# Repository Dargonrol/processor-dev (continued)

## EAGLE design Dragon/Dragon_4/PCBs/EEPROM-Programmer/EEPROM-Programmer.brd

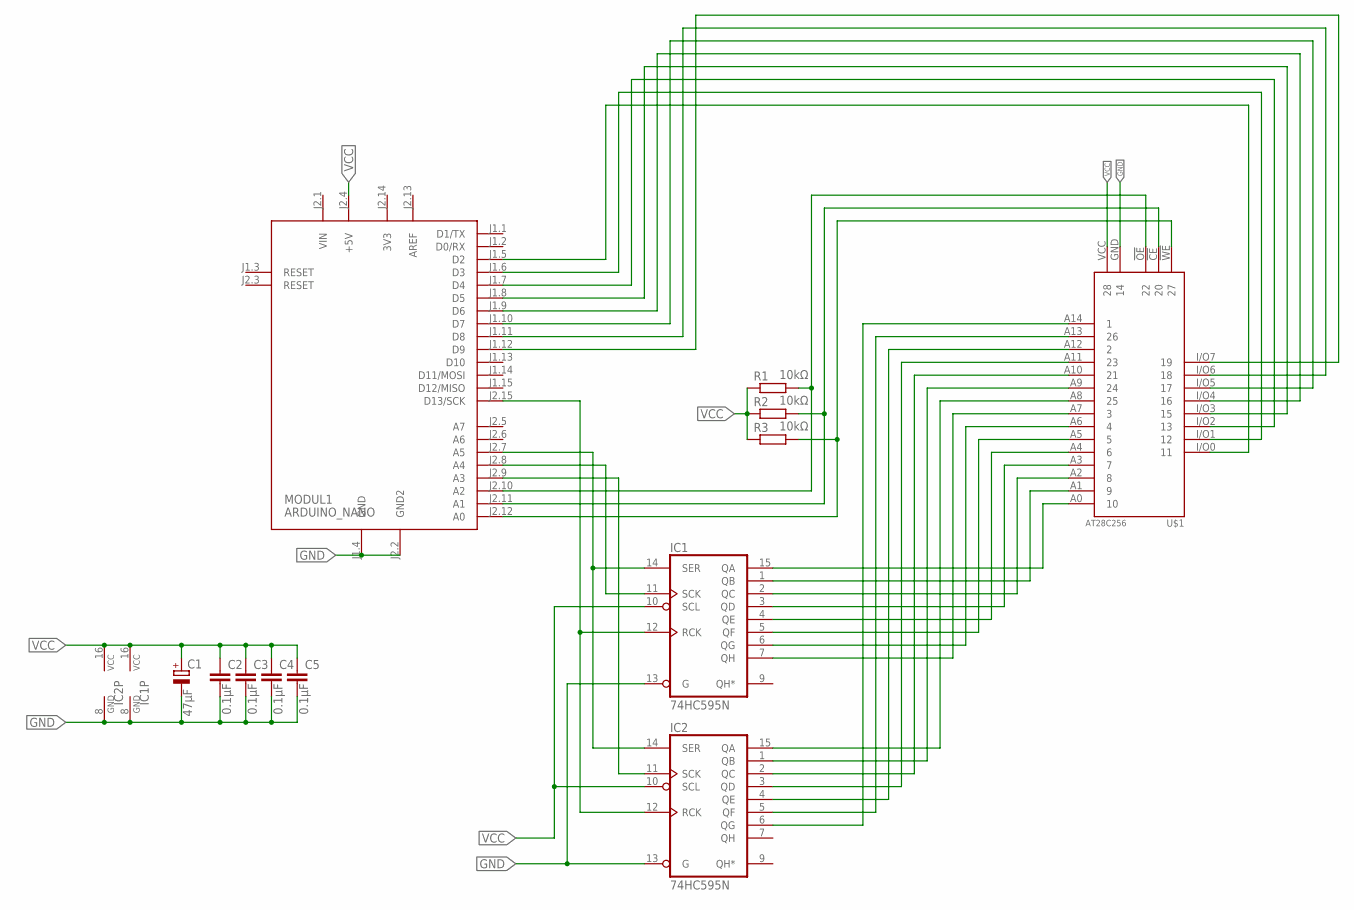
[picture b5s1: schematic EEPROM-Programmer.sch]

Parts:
C1: 47µF; E2,5-6E
C2, C3, C4, C5: 0.1µF; C2.5-3
IC1, IC2: 74HC595N; DIL16
MODUL1: ARDUINO_NANO; ARDUINO_NANO2
R1, R2, R3: 10kΩ; 0204/7
U$1: AT28C256

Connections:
3V3: MODUL1.J2.14 (3V3)
AREF: MODUL1.J2.13 (AREF)
GND: C1.-, C2.2, C3.2, C4.2, C5.2, IC1.8 (GND), IC1.13 (G), IC2.8 (GND), IC2.13 (G), MODUL1.J1.4 (GND), MODUL1.J2.2 (GND2), U$1.GND (14)
unnamed: IC1.15 (QA), U$1.A0 (10)
unnamed: IC1.1 (QB), U$1.A1 (9)
unnamed: IC1.2 (QC), U$1.A2 (8)
unnamed: IC1.3 (QD), U$1.A3 (7)
unnamed: IC1.4 (QE), U$1.A4 (6)
unnamed: IC1.5 (QF), U$1.A5 (5)
unnamed: IC1.6 (QG), U$1.A6 (4)
unnamed: IC1.7 (QH), U$1.A7 (3)
unnamed: IC2.15 (QA), U$1.A8 (25)
unnamed: IC2.1 (QB), U$1.A9 (24)
unnamed: IC2.2 (QC), U$1.A10 (21)
unnamed: IC2.3 (QD), U$1.A11 (23)
unnamed: IC2.4 (QE), U$1.A12 (2)
unnamed: IC2.5 (QF), U$1.A13 (26)
unnamed: IC2.6 (QG), U$1.A14 (1)
unnamed: MODUL1.J1.5 (D2), U$1.I/O0 (11)
unnamed: MODUL1.J2.12 (A0), R3.2, U$1.!WE (27)
unnamed: MODUL1.J1.6 (D3), U$1.I/O1 (12)
unnamed: MODUL1.J1.7 (D4), U$1.I/O2 (13)
unnamed: MODUL1.J1.8 (D5), U$1.I/O3 (15)
unnamed: MODUL1.J1.9 (D6), U$1.I/O4 (16)
unnamed: MODUL1.J1.10 (D7), U$1.I/O5 (17)
unnamed: MODUL1.J1.11 (D8), U$1.I/O6 (18)
unnamed: MODUL1.J1.12 (D9), U$1.I/O7 (19)
unnamed: MODUL1.J2.11 (A1), R2.2, U$1.!CE (20)
unnamed: MODUL1.J2.10 (A2), R1.2, U$1.!OE (22)
unnamed: IC2.11 (SCK), MODUL1.J2.9 (A3)
unnamed: IC1.11 (SCK), MODUL1.J2.8 (A4)
unnamed: IC1.14 (SER), IC2.14 (SER), MODUL1.J2.7 (A5)
unnamed: IC1.12 (RCK), IC2.12 (RCK), MODUL1.J2.15 (D13/SCK)
VCC: C1.+, C2.1, C3.1, C4.1, C5.1, IC1.10 (SCL), IC1.16 (VCC), IC2.10 (SCL), IC2.16 (VCC), MODUL1.J2.4 (+5V), R1.1, R2.1, R3.1, U$1.VCC (28)
VIN: MODUL1.J2.1 (VIN)

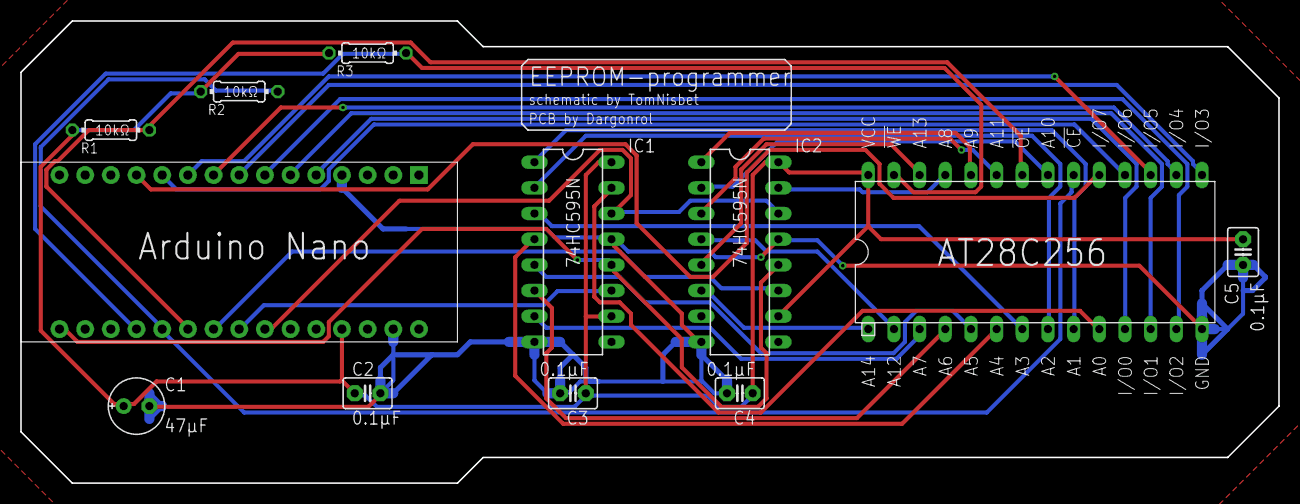
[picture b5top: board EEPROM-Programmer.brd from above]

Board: 2 copper layers, 124.5 x 45.7 mm, 12 parts (0 on the bottom side), 32 nets.

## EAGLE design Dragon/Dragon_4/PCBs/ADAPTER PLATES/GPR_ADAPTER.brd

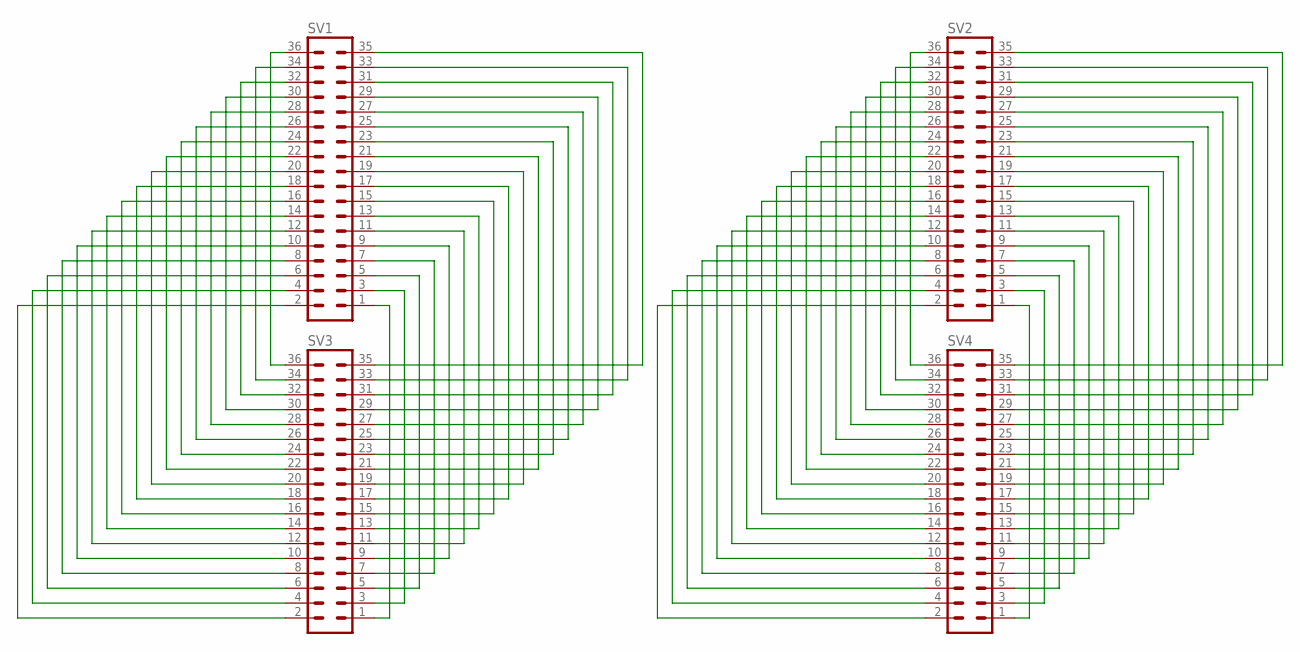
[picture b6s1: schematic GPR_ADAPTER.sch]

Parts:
SV1, SV2, SV3, SV4: MA18-2

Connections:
unnamed: SV1.36, SV3.36
unnamed: SV1.34, SV3.34
unnamed: SV1.32, SV3.32
unnamed: SV1.30, SV3.30
unnamed: SV1.28, SV3.28
unnamed: SV1.26, SV3.26
unnamed: SV1.24, SV3.24
unnamed: SV1.22, SV3.22
unnamed: SV1.20, SV3.20
unnamed: SV1.18, SV3.18
unnamed: SV1.16, SV3.16
unnamed: SV1.14, SV3.14
unnamed: SV1.12, SV3.12
unnamed: SV1.10, SV3.10
unnamed: SV1.8, SV3.8
unnamed: SV1.6, SV3.6
unnamed: SV1.4, SV3.4
unnamed: SV1.2, SV3.2
unnamed: SV2.34, SV4.34
unnamed: SV2.32, SV4.32
unnamed: SV2.30, SV4.30
unnamed: SV2.28, SV4.28
unnamed: SV2.26, SV4.26
unnamed: SV2.24, SV4.24
unnamed: SV2.22, SV4.22
unnamed: SV2.20, SV4.20
unnamed: SV2.18, SV4.18
unnamed: SV2.16, SV4.16
unnamed: SV2.14, SV4.14
unnamed: SV2.12, SV4.12
unnamed: SV2.10, SV4.10
unnamed: SV2.8, SV4.8
unnamed: SV2.6, SV4.6
unnamed: SV2.4, SV4.4
unnamed: SV2.2, SV4.2
unnamed: SV2.36, SV4.36
unnamed: SV1.3, SV3.3
unnamed: SV1.5, SV3.5
unnamed: SV1.7, SV3.7
unnamed: SV1.9, SV3.9
unnamed: SV1.11, SV3.11
unnamed: SV1.13, SV3.13
unnamed: SV1.15, SV3.15
unnamed: SV1.17, SV3.17
unnamed: SV1.19, SV3.19
unnamed: SV1.21, SV3.21
unnamed: SV1.23, SV3.23
unnamed: SV1.25, SV3.25
unnamed: SV1.27, SV3.27
unnamed: SV1.29, SV3.29
unnamed: SV1.31, SV3.31
unnamed: SV1.33, SV3.33
unnamed: SV1.35, SV3.35
unnamed: SV1.1, SV3.1
unnamed: SV2.3, SV4.3
unnamed: SV2.5, SV4.5
unnamed: SV2.7, SV4.7
unnamed: SV2.9, SV4.9
unnamed: SV2.11, SV4.11
unnamed: SV2.13, SV4.13
unnamed: SV2.15, SV4.15
unnamed: SV2.17, SV4.17
unnamed: SV2.19, SV4.19
unnamed: SV2.21, SV4.21
unnamed: SV2.23, SV4.23
unnamed: SV2.25, SV4.25
unnamed: SV2.27, SV4.27
unnamed: SV2.29, SV4.29
unnamed: SV2.31, SV4.31
unnamed: SV2.33, SV4.33
unnamed: SV2.35, SV4.35
unnamed: SV2.1, SV4.1

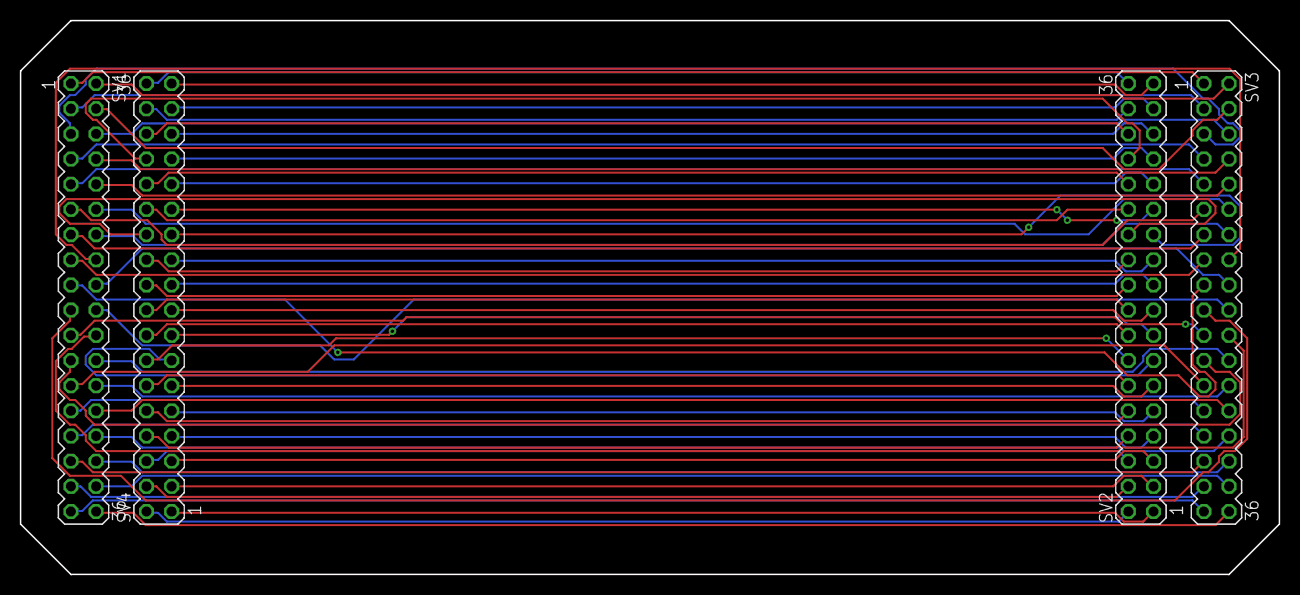
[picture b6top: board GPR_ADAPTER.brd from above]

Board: 2 copper layers, 127.0 x 55.9 mm, 4 parts (0 on the bottom side), 72 nets.

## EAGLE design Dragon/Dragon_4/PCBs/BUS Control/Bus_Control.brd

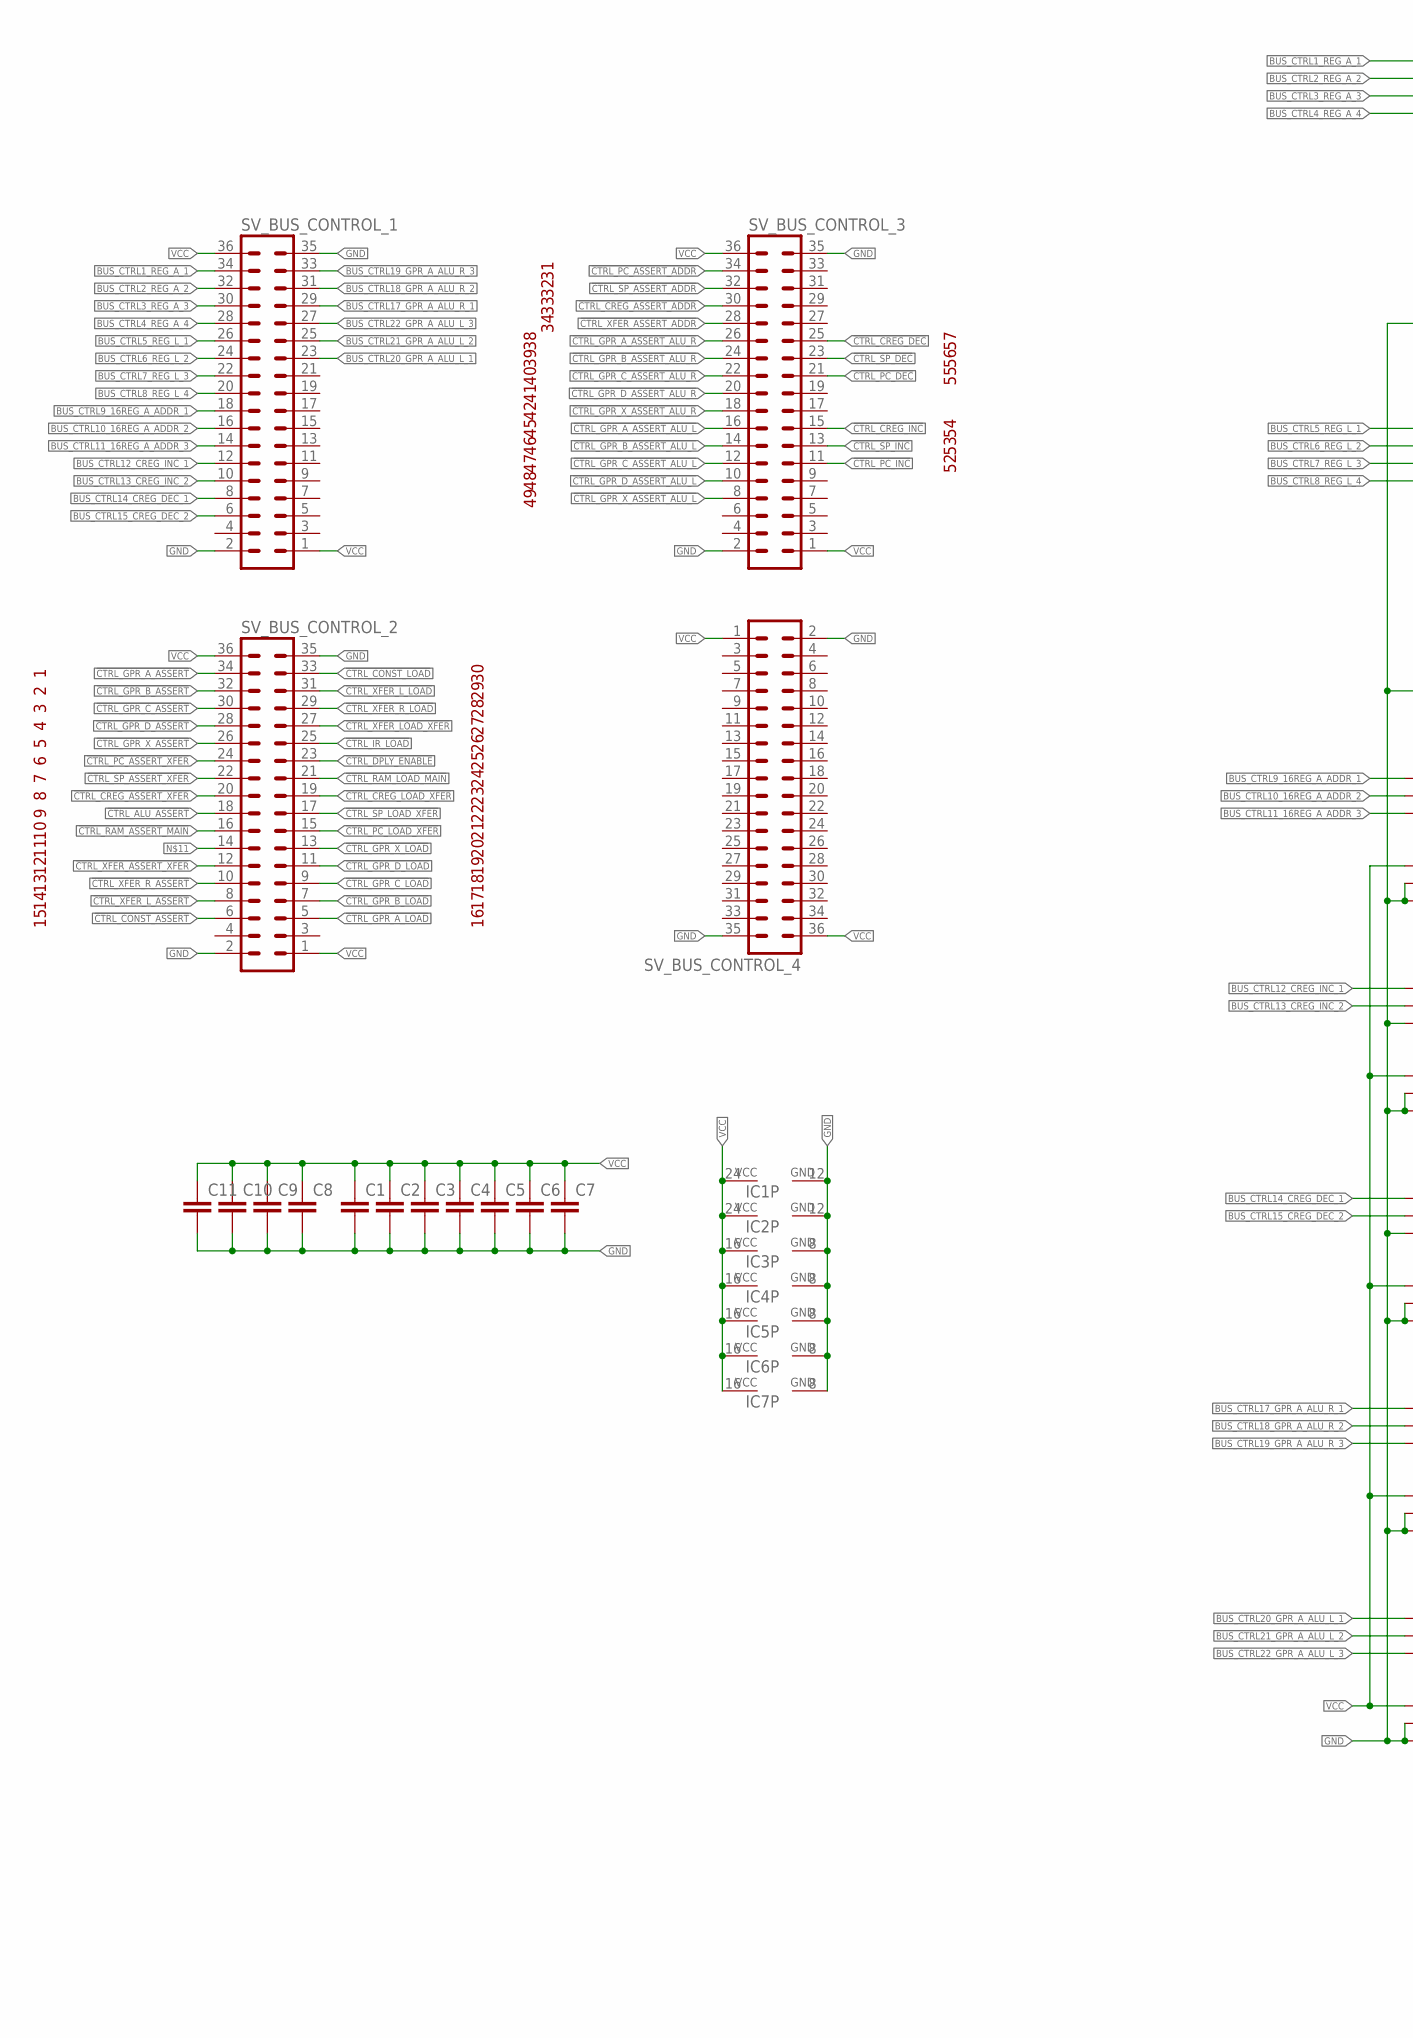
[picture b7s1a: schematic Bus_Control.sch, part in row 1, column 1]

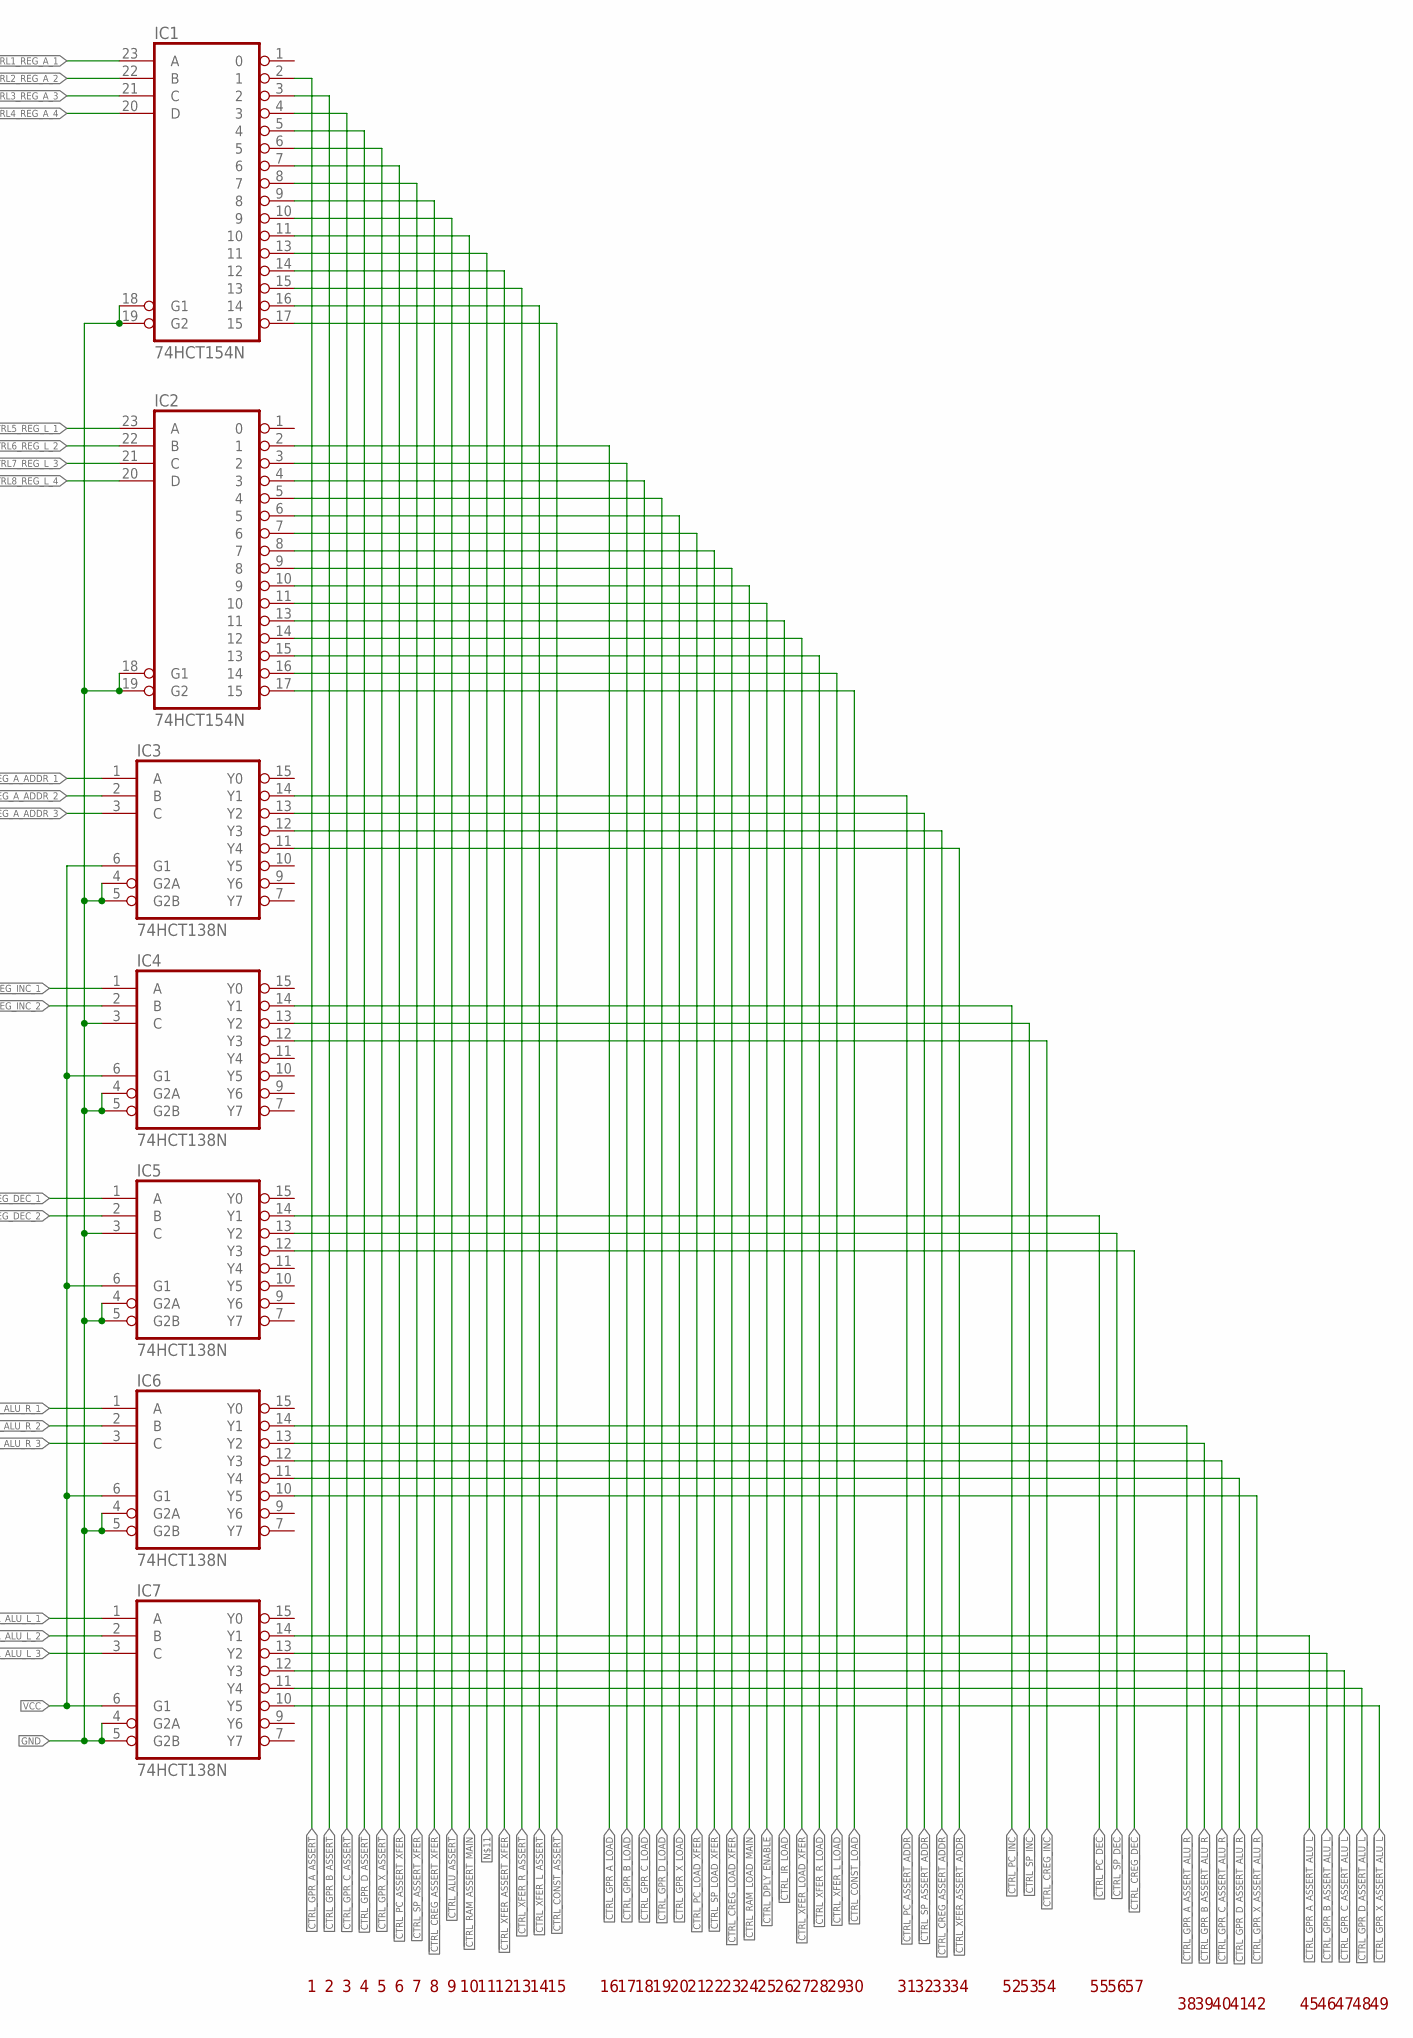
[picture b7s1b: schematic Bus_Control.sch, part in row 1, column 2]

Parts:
C1, C2, C3, C4, C5, C6, C7, C8, C9, C10, C11: C-EUC0805; C0805
IC1, IC2: 74HCT154N; DIL24-6
IC3, IC4, IC5, IC6, IC7: 74HCT138N; DIL16
SV_BUS_CONTROL_1, SV_BUS_CONTROL_2, SV_BUS_CONTROL_3, SV_BUS_CONTROL_4: MA18-2

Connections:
!CTRL_ALU_ASSERT: IC1.10 (9), SV_BUS_CONTROL_2.18
!CTRL_CONST_ASSERT: IC1.17 (15), SV_BUS_CONTROL_2.6
!CTRL_CONST_LOAD: IC2.17 (15), SV_BUS_CONTROL_2.33
!CTRL_CREG_ASSERT_ADDR: IC3.12 (Y3), SV_BUS_CONTROL_3.30
!CTRL_CREG_ASSERT_XFER: IC1.9 (8), SV_BUS_CONTROL_2.20
!CTRL_CREG_DEC: IC5.12 (Y3), SV_BUS_CONTROL_3.25
!CTRL_CREG_INC: IC4.12 (Y3), SV_BUS_CONTROL_3.15
!CTRL_CREG_LOAD_XFER: IC2.9 (8), SV_BUS_CONTROL_2.19
!CTRL_DPLY_ENABLE: IC2.11 (10), SV_BUS_CONTROL_2.23
!CTRL_GPR_A_ASSERT: IC1.2 (1), SV_BUS_CONTROL_2.34
!CTRL_GPR_A_ASSERT_ALU_L: IC7.14 (Y1), SV_BUS_CONTROL_3.16
!CTRL_GPR_A_ASSERT_ALU_R: IC6.14 (Y1), SV_BUS_CONTROL_3.26
!CTRL_GPR_A_LOAD: IC2.2 (1), SV_BUS_CONTROL_2.5
!CTRL_GPR_B_ASSERT: IC1.3 (2), SV_BUS_CONTROL_2.32
!CTRL_GPR_B_ASSERT_ALU_L: IC7.13 (Y2), SV_BUS_CONTROL_3.14
!CTRL_GPR_B_ASSERT_ALU_R: IC6.13 (Y2), SV_BUS_CONTROL_3.24
!CTRL_GPR_B_LOAD: IC2.3 (2), SV_BUS_CONTROL_2.7
!CTRL_GPR_C_ASSERT: IC1.4 (3), SV_BUS_CONTROL_2.30
!CTRL_GPR_C_ASSERT_ALU_L: IC7.12 (Y3), SV_BUS_CONTROL_3.12
!CTRL_GPR_C_ASSERT_ALU_R: IC6.12 (Y3), SV_BUS_CONTROL_3.22
!CTRL_GPR_C_LOAD: IC2.4 (3), SV_BUS_CONTROL_2.9
!CTRL_GPR_D_ASSERT: IC1.5 (4), SV_BUS_CONTROL_2.28
!CTRL_GPR_D_ASSERT_ALU_L: IC7.11 (Y4), SV_BUS_CONTROL_3.10
!CTRL_GPR_D_ASSERT_ALU_R: IC6.11 (Y4), SV_BUS_CONTROL_3.20
!CTRL_GPR_D_LOAD: IC2.5 (4), SV_BUS_CONTROL_2.11
!CTRL_GPR_X_ASSERT: IC1.6 (5), SV_BUS_CONTROL_2.26
!CTRL_GPR_X_ASSERT_ALU_L: IC7.10 (Y5), SV_BUS_CONTROL_3.8
!CTRL_GPR_X_ASSERT_ALU_R: IC6.10 (Y5), SV_BUS_CONTROL_3.18
!CTRL_GPR_X_LOAD: IC2.6 (5), SV_BUS_CONTROL_2.13
!CTRL_IR_LOAD: IC2.13 (11), SV_BUS_CONTROL_2.25
!CTRL_PC_ASSERT_ADDR: IC3.14 (Y1), SV_BUS_CONTROL_3.34
!CTRL_PC_ASSERT_XFER: IC1.7 (6), SV_BUS_CONTROL_2.24
!CTRL_PC_DEC: IC5.14 (Y1), SV_BUS_CONTROL_3.21
!CTRL_PC_INC: IC4.14 (Y1), SV_BUS_CONTROL_3.11
!CTRL_PC_LOAD_XFER: IC2.7 (6), SV_BUS_CONTROL_2.15
!CTRL_RAM_ASSERT_MAIN: IC1.11 (10), SV_BUS_CONTROL_2.16
!CTRL_RAM_LOAD_MAIN: IC2.10 (9), SV_BUS_CONTROL_2.21
!CTRL_SP_ASSERT_ADDR: IC3.13 (Y2), SV_BUS_CONTROL_3.32
!CTRL_SP_ASSERT_XFER: IC1.8 (7), SV_BUS_CONTROL_2.22
!CTRL_SP_DEC: IC5.13 (Y2), SV_BUS_CONTROL_3.23
!CTRL_SP_INC: IC4.13 (Y2), SV_BUS_CONTROL_3.13
!CTRL_SP_LOAD_XFER: IC2.8 (7), SV_BUS_CONTROL_2.17
!CTRL_XFER_ASSERT_ADDR: IC3.11 (Y4), SV_BUS_CONTROL_3.28
!CTRL_XFER_ASSERT_XFER: IC1.14 (12), SV_BUS_CONTROL_2.12
!CTRL_XFER_LOAD_XFER: IC2.14 (12), SV_BUS_CONTROL_2.27
!CTRL_XFER_L_ASSERT: IC1.16 (14), SV_BUS_CONTROL_2.8
!CTRL_XFER_L_LOAD: IC2.16 (14), SV_BUS_CONTROL_2.31
!CTRL_XFER_R_ASSERT: IC1.15 (13), SV_BUS_CONTROL_2.10
!CTRL_XFER_R_LOAD: IC2.15 (13), SV_BUS_CONTROL_2.29
BUS_CTRL1_REG_A_1: IC1.23 (A), SV_BUS_CONTROL_1.34
BUS_CTRL2_REG_A_2: IC1.22 (B), SV_BUS_CONTROL_1.32
BUS_CTRL3_REG_A_3: IC1.21 (C), SV_BUS_CONTROL_1.30
BUS_CTRL4_REG_A_4: IC1.20 (D), SV_BUS_CONTROL_1.28
BUS_CTRL5_REG_L_1: IC2.23 (A), SV_BUS_CONTROL_1.26
BUS_CTRL6_REG_L_2: IC2.22 (B), SV_BUS_CONTROL_1.24
BUS_CTRL7_REG_L_3: IC2.21 (C), SV_BUS_CONTROL_1.22
BUS_CTRL8_REG_L_4: IC2.20 (D), SV_BUS_CONTROL_1.20
BUS_CTRL9_16REG_A_ADDR_1: IC3.1 (A), SV_BUS_CONTROL_1.18
BUS_CTRL10_16REG_A_ADDR_2: IC3.2 (B), SV_BUS_CONTROL_1.16
BUS_CTRL11_16REG_A_ADDR_3: IC3.3 (C), SV_BUS_CONTROL_1.14
BUS_CTRL12_CREG_INC_1: IC4.1 (A), SV_BUS_CONTROL_1.12
BUS_CTRL13_CREG_INC_2: IC4.2 (B), SV_BUS_CONTROL_1.10
BUS_CTRL14_CREG_DEC_1: IC5.1 (A), SV_BUS_CONTROL_1.8
BUS_CTRL15_CREG_DEC_2: IC5.2 (B), SV_BUS_CONTROL_1.6
BUS_CTRL17_GPR_A_ALU_R_1: IC6.1 (A), SV_BUS_CONTROL_1.29
BUS_CTRL18_GPR_A_ALU_R_2: IC6.2 (B), SV_BUS_CONTROL_1.31
BUS_CTRL19_GPR_A_ALU_R_3: IC6.3 (C), SV_BUS_CONTROL_1.33
BUS_CTRL20_GPR_A_ALU_L_1: IC7.1 (A), SV_BUS_CONTROL_1.23
BUS_CTRL21_GPR_A_ALU_L_2: IC7.2 (B), SV_BUS_CONTROL_1.25
BUS_CTRL22_GPR_A_ALU_L_3: IC7.3 (C), SV_BUS_CONTROL_1.27
GND: C1.2, C2.2, C3.2, C4.2, C5.2, C6.2, C7.2, C8.2, C9.2, C10.2, C11.2, IC1.12 (GND), IC1.18 (G1), IC1.19 (G2), IC2.12 (GND), IC2.18 (G1), IC2.19 (G2), IC3.4 (G2A), IC3.5 (G2B), IC3.8 (GND), IC4.3 (C), IC4.4 (G2A), IC4.5 (G2B), IC4.8 (GND), IC5.3 (C), IC5.4 (G2A), IC5.5 (G2B), IC5.8 (GND), IC6.4 (G2A), IC6.5 (G2B), IC6.8 (GND), IC7.4 (G2A), IC7.5 (G2B), IC7.8 (GND), SV_BUS_CONTROL_1.2, SV_BUS_CONTROL_1.35, SV_BUS_CONTROL_2.2, SV_BUS_CONTROL_2.35, SV_BUS_CONTROL_3.2, SV_BUS_CONTROL_3.35, SV_BUS_CONTROL_4.2, SV_BUS_CONTROL_4.35
unnamed: IC1.13 (11), SV_BUS_CONTROL_2.14
VCC: C1.1, C2.1, C3.1, C4.1, C5.1, C6.1, C7.1, C8.1, C9.1, C10.1, C11.1, IC1.24 (VCC), IC2.24 (VCC), IC3.6 (G1), IC3.16 (VCC), IC4.6 (G1), IC4.16 (VCC), IC5.6 (G1), IC5.16 (VCC), IC6.6 (G1), IC6.16 (VCC), IC7.6 (G1), IC7.16 (VCC), SV_BUS_CONTROL_1.1, SV_BUS_CONTROL_1.36, SV_BUS_CONTROL_2.1, SV_BUS_CONTROL_2.36, SV_BUS_CONTROL_3.1, SV_BUS_CONTROL_3.36, SV_BUS_CONTROL_4.1, SV_BUS_CONTROL_4.36

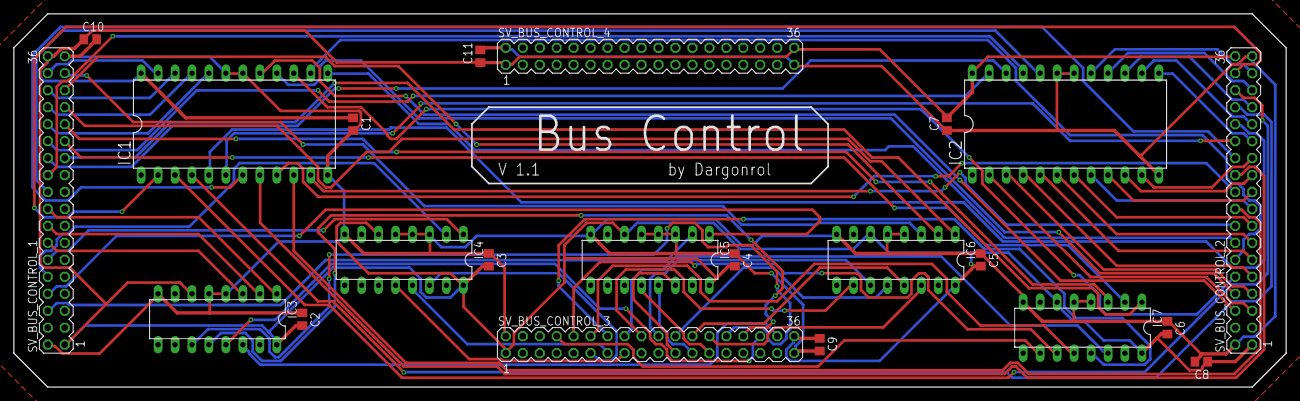
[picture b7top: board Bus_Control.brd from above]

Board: 2 copper layers, 190.5 x 55.9 mm, 22 parts (0 on the bottom side), 73 nets.
